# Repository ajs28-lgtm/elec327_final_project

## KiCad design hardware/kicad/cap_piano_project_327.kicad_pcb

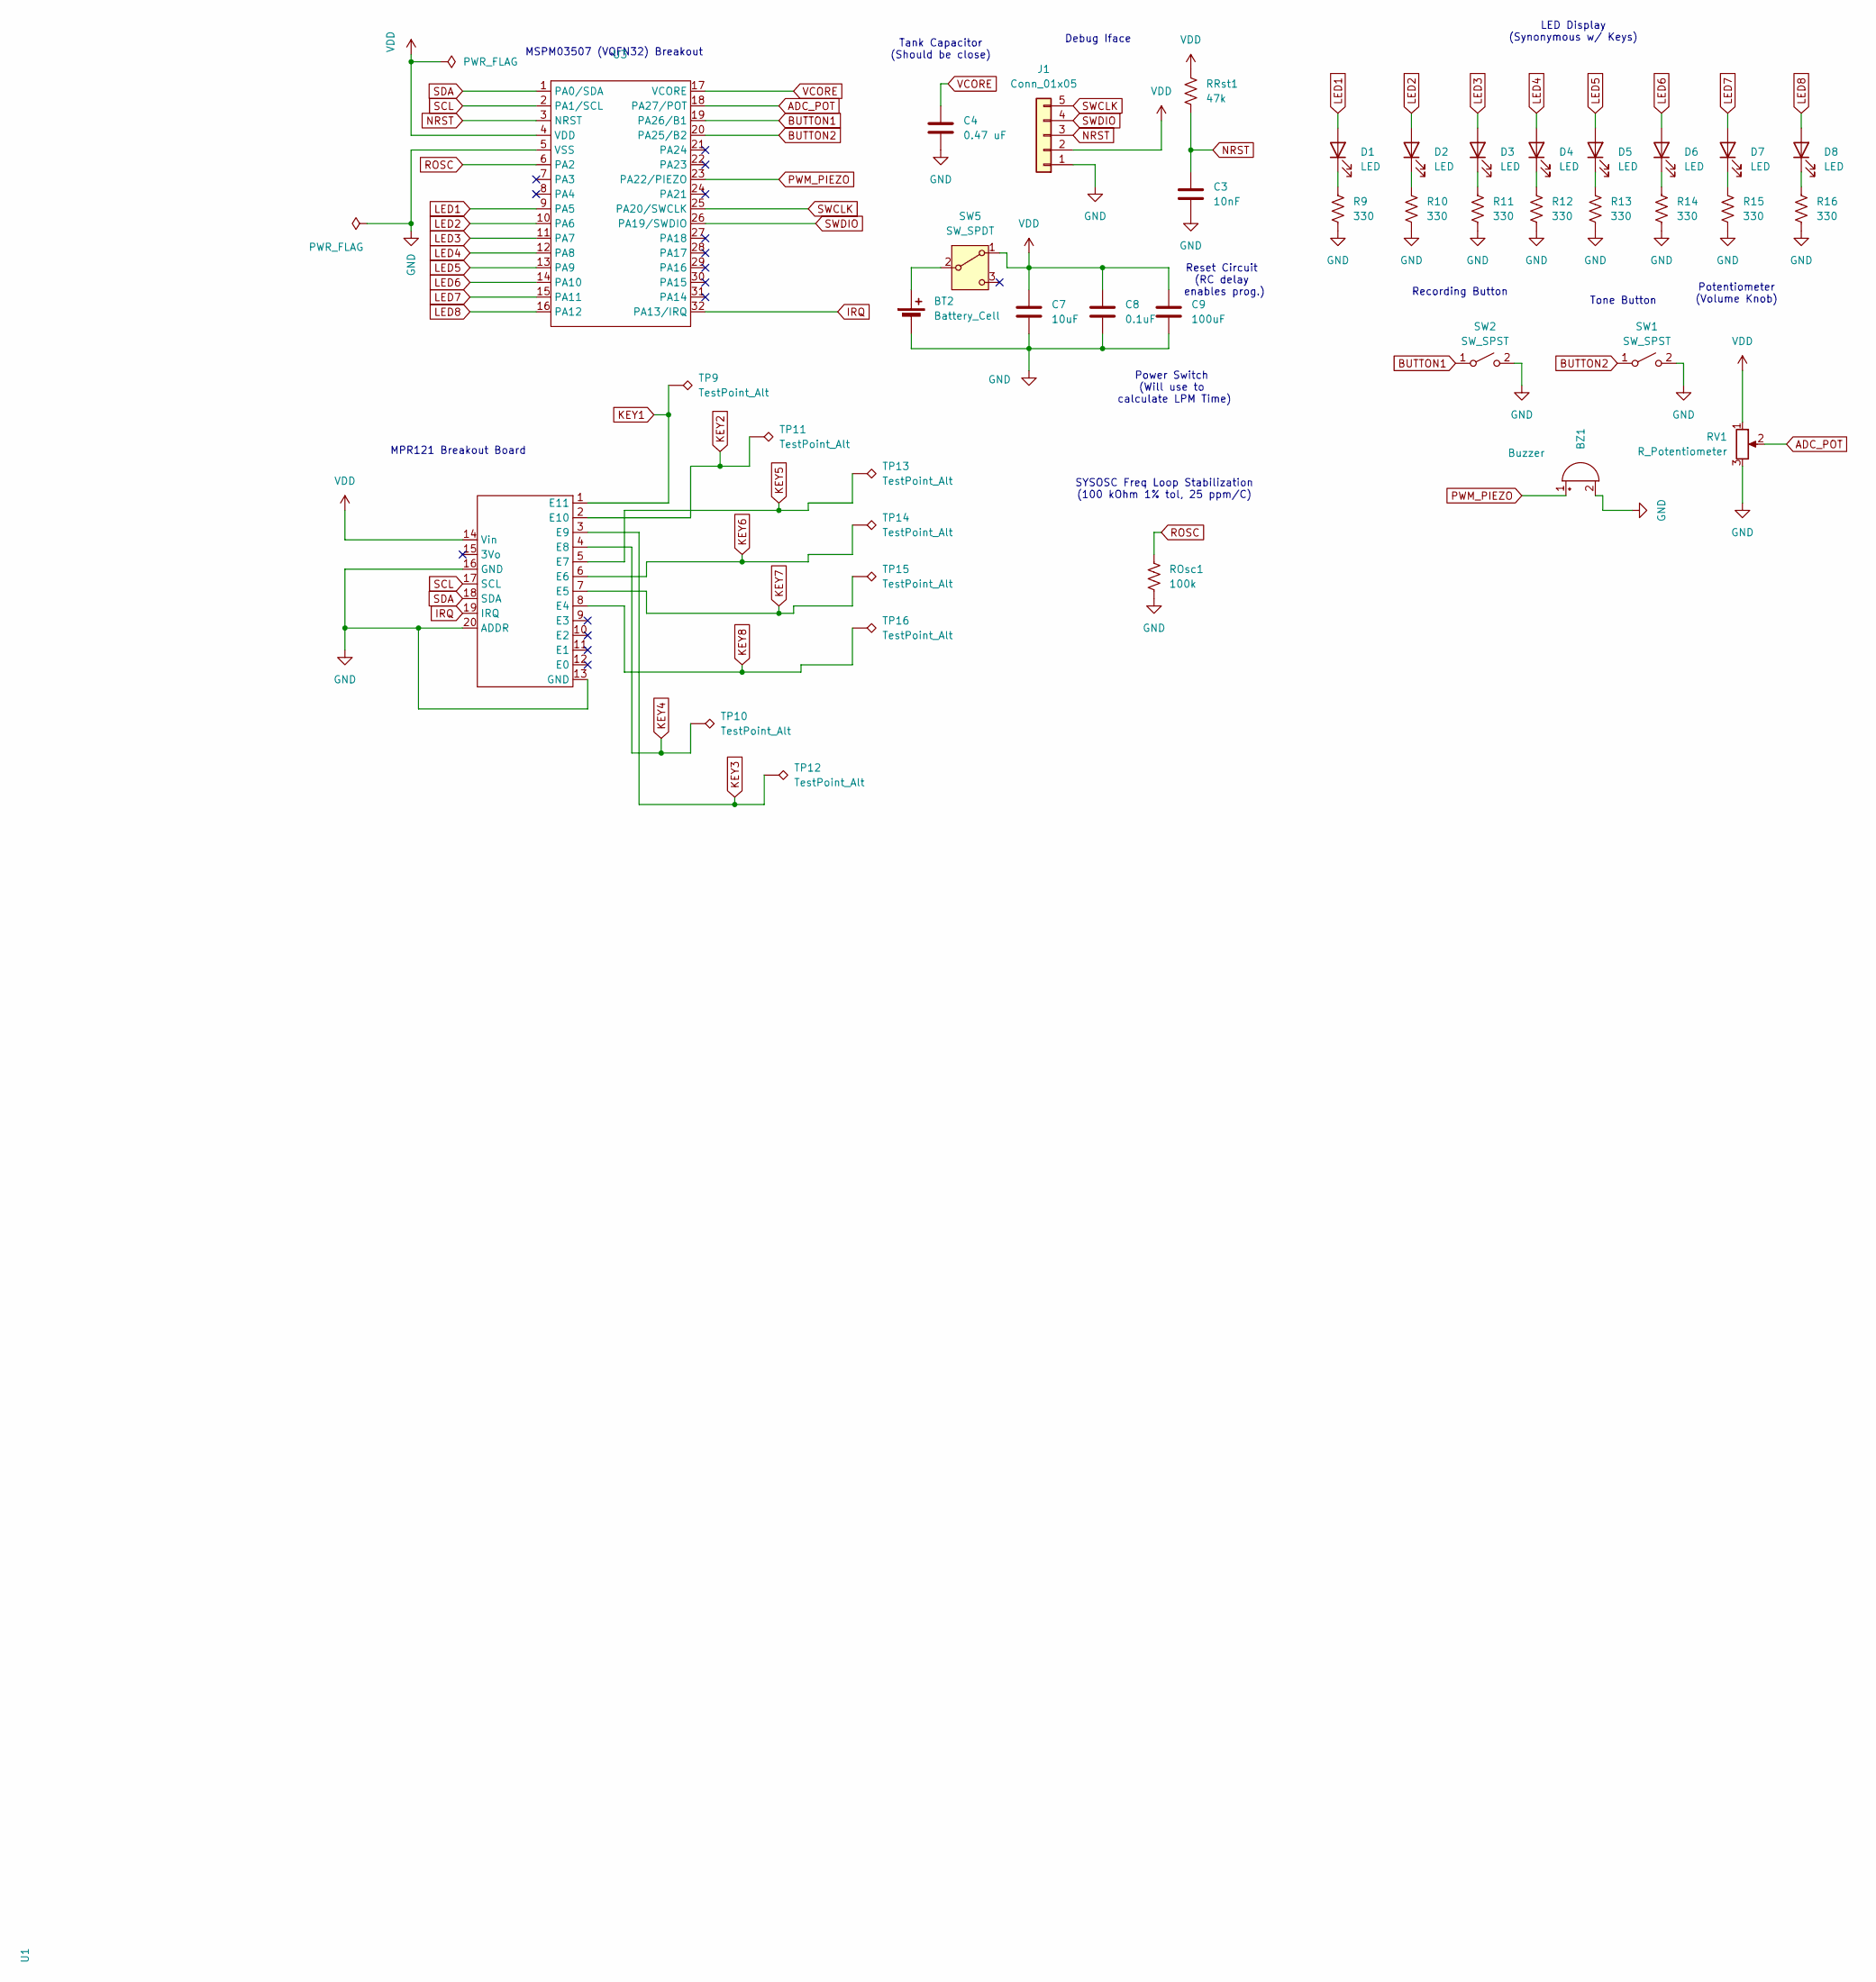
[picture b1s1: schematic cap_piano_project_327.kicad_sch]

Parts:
BT2: Battery_Cell; BatteryHolder_Keystone_1060_1x2032; MPN C7498148; LCSC Part # C7498148
BZ1: Buzzer; Buzzer_TDK_PS1240P02BT_D12.2mm_H6.5mm
C3: 10nF; C_1206_3216Metric_Pad1.33x1.80mm_HandSolder
C4: 0.47 uF; C_1206_3216Metric_Pad1.33x1.80mm_HandSolder
C7: 10uF; C_1206_3216Metric_Pad1.33x1.80mm_HandSolder; LCSC Part # C19702
C8: 0.1uF; C_1206_3216Metric_Pad1.33x1.80mm_HandSolder; LCSC Part # C1591
C9: 100uF; C_1206_3216Metric_Pad1.33x1.80mm_HandSolder; LCSC Part # C15008
D1, D2, D3, D4, D5, D6, D7, D8: LED; LED_D5.0mm
J1: Conn_01x05; PinHeader_1x05_P2.54mm_Vertical; MPN C492413
R9, R10, R11, R12, R13, R14, R15, R16: 330; R_1206_3216Metric
ROsc1: 100k; R_1206_3216Metric
RRst1: 47k; R_1206_3216Metric
RV1: R_Potentiometer; Potentiometer_Alpha_RD901F-40-00D_Single_Vertical
SW1, SW2: SW_SPST; SW_PUSH_6mm_H5mm
SW5: SW_SPDT; SW_Slide-03_Wuerth-WS-SLTV_10x2.5x6.4_P2.54mm; MPN C20611678; LCSC Part # C20611678
TP9, TP10, TP11, TP12, TP13, TP14, TP15, TP16: TestPoint_Alt; TestPoint_Pad_4.0x4.0mm
U1: Adafruit_MPR121_1982_Socket
U3: SMT Breakout PCB - 32-QFN

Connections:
ADC_POT: RV1.2, U3.18 (PA27/POT)
BUTTON1: SW2.1 (A), U3.19 (PA26/B1)
BUTTON2: SW1.1 (A), U3.20 (PA25/B2)
GND: BT2.2 (-), BZ1.2 (-), C3.2, C4.2, C7.2, C8.2, C9.2, J1.1, R9.1, R10.1, R11.1, R12.1, R13.1, R14.1, R15.1, R16.1, ROsc1.1, RV1.3, SW1.2 (B), SW2.2 (B), U1.13 (GND), U1.16 (GND), U1.20 (ADDR), U3.5 (VSS)
IRQ: U1.19 (IRQ), U3.32 (PA13/IRQ)
KEY1: TP9.1, U1.1 (E11)
KEY2: TP11.1, U1.2 (E10)
KEY3: TP12.1, U1.3 (E9)
KEY4: TP10.1, U1.4 (E8)
KEY5: TP13.1, U1.5 (E7)
KEY6: TP14.1, U1.6 (E6)
KEY7: TP15.1, U1.7 (E5)
KEY8: TP16.1, U1.8 (E4)
LED1: D1.2 (A), U3.9 (PA5)
LED2: D2.2 (A), U3.10 (PA6)
LED3: D3.2 (A), U3.11 (PA7)
LED4: D4.2 (A), U3.12 (PA8)
LED5: D5.2 (A), U3.13 (PA9)
LED6: D6.2 (A), U3.14 (PA10)
LED7: D7.2 (A), U3.15 (PA11)
LED8: D8.2 (A), U3.16 (PA12)
NRST: C3.1, J1.3, RRst1.1, U3.3 (NRST)
unnamed: BT2.1 (+), SW5.2 (B)
unnamed: D1.1 (K), R9.2
unnamed: D2.1 (K), R10.2
unnamed: D3.1 (K), R11.2
unnamed: D4.1 (K), R12.2
unnamed: D5.1 (K), R13.2
unnamed: D6.1 (K), R14.2
unnamed: D7.1 (K), R15.2
unnamed: D8.1 (K), R16.2
PWM_PIEZO: BZ1.1 (+), U3.23 (PA22/PIEZO)
ROSC: ROsc1.2, U3.6 (PA2)
SCL: U1.17 (SCL), U3.2 (PA1/SCL)
SDA: U1.18 (SDA), U3.1 (PA0/SDA)
SWCLK: J1.5, U3.25 (PA20/SWCLK)
SWDIO: J1.4, U3.26 (PA19/SWDIO)
VCORE: C4.1, U3.17 (VCORE)
VDD: C7.1, C8.1, C9.1, J1.2, RRst1.2, RV1.1, SW5.1 (A), U1.14 (Vin), U3.4 (VDD)

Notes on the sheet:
Power Switch (Will use to calculate LPM Time)
Recording Button
LED Display (Synonymous w/ Keys)
SYSOSC Freq Loop Stabilization (100 kOhm 1% tol, 25 ppm/C)
MSPM03507 (VQFN32) Breakout
Tank Capacitor (Should be close)
Potentiometer (Volume Knob)
Tone Button
Debug Iface
MPR121 Breakout Board
Reset Circuit (RC delay enables prog.)

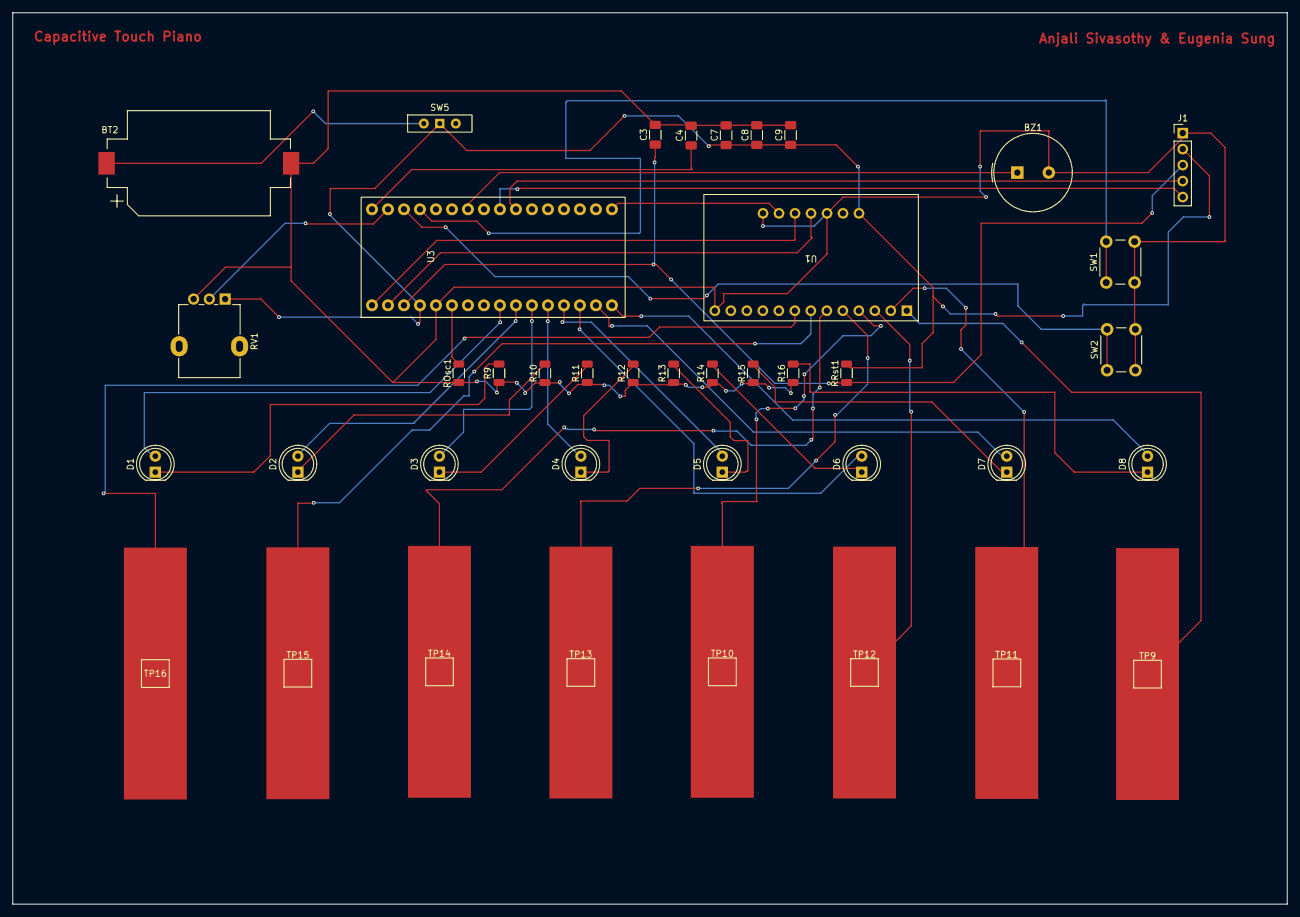
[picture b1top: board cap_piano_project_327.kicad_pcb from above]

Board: 2 copper layers, 202.4 x 141.5 mm, 40 parts (0 on the bottom side), 39 nets.

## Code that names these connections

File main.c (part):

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// HARDWARE DEFINITIONS & PIN MAPPING
// ============================================================================

// LEDs (PA5 to PA12)
#define LED1 (1u << 5)
#define LED2 (1u << 6)
#define LED3 (1u << 7)
#define LED4 (1u << 8)
#define LED5 (1u << 9)
#define LED6 (1u << 10)
#define LED7 (1u << 11)
#define LED8 (1u << 12)
#define LED_ALL (LED1 | LED2 | LED3 | LED4 | LED5 | LED6 | LED7 | LED8)

// Buzzer (PA22)
#define BUZZER (1u << 22)

// I2C and IRQ Pins
#define SDA_PIN (1u << 0)  // PA0
#define SCL_PIN (1u << 1)  // PA1
#define IRQ_PIN (1u << 13) // PA13

// Buttons are wired to GND
// They are active-low and need internal pull-ups
#define BUTTON_OCTAVE (1u << 26) // PA26 / BUTTON1
#define BUTTON_RECORD (1u << 25) // PA25 / BUTTON2
#define CONTROL_PINS (BUTTON_OCTAVE | BUTTON_RECORD)

// ADC potentiometer input
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
    // Configure PINCM for LEDs (Output)
    // 0x81 = PC (bit 7) + GPIO function (bit 0)
    IOMUX->SECCFG.PINCM[IOMUX_PINCM10] = 0x81; // PA5 LED1
    IOMUX->SECCFG.PINCM[IOMUX_PINCM11] = 0x81; // PA6 LED2
    IOMUX->SECCFG.PINCM[IOMUX_PINCM14] = 0x81; // PA7 LED3
    IOMUX->SECCFG.PINCM[IOMUX_PINCM19] = 0x81; // PA8 LED4
    IOMUX->SECCFG.PINCM[IOMUX_PINCM20] = 0x81; // PA9 LED5
    IOMUX->SECCFG.PINCM[IOMUX_PINCM21] = 0x81; // PA10 LED6
    IOMUX->SECCFG.PINCM[IOMUX_PINCM22] = 0x81; // PA11 LED7
    IOMUX->SECCFG.PINCM[IOMUX_PINCM34] = 0x81; // PA12 LED8

    // Configure PINCM for Buzzer (Output)
    IOMUX->SECCFG.PINCM[IOMUX_PINCM47] = 0x81; // PA22

    // Configure PINCM for MPR121 IRQ (Input)
    // CRITICAL FIX: Must set INENA (bit 18) to enable the input buffer!
    // 0x40081 = INENA (bit 18) + PC (bit 7) + GPIO function (bit 0)
    IOMUX->SECCFG.PINCM[IOMUX_PINCM35] = 0x40081; // PA13

    // Configure PINCM for Soft I2C (Open-Drain style)
    // Also need INENA (bit 18) so we can read SDA/SCL state
    IOMUX->SECCFG.PINCM[IOMUX_PINCM1] = 0x40081; // PA0 SDA
    IOMUX->SECCFG.PINCM[IOMUX_PINCM2] = 0x40081; // PA1 SCL

    // Configure user buttons as GPIO inputs with pull-ups
    // 0x60081 = pull-up + input enable + peripheral connected + GPIO function
    // PA26 is PINCM59 and PA25 is PINCM55 on MSPM0G3507
    IOMUX->SECCFG.PINCM[IOMUX_PINCM59] = 0x60081; // PA26 / BUTTON1 / octave
    IOMUX->SECCFG.PINCM[IOMUX_PINCM55] = 0x60081; // PA25 / BUTTON2 / record

    // Configure PA27/POT for analog use
    // For analog functions, PINCM.PF and PINCM.PC should be 0, 
    // so do not connect it as a digital GPIO
    IOMUX->SECCFG.PINCM[IOMUX_PINCM60] = 0x00000000; // PA27 / A0_0

    // Set output values to 0 initially
    GPIOA->DOUTCLR31_0 = LED_ALL | BUZZER | SDA_PIN | SCL_PIN;
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    DL_ADC12_setSampleTime0(ADC0, 32);
    DL_ADC12_configConversionMem(ADC0,
                                 DL_ADC12_MEM_IDX_0,
                                 DL_ADC12_INPUT_CHAN_0, // PA27 / A0_0
                                 DL_ADC12_REFERENCE_VOLTAGE_VDDA,
                                 DL_ADC12_SAMPLE_TIMER_SOURCE_SCOMP0,
                                 DL_ADC12_AVERAGING_MODE_DISABLED,
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        // Diagnostic: Init Failed
        // Blink LED1 and LED8 alternately
        while (1) {
            GPIOA->DOUTSET31_0 = LED1;
            GPIOA->DOUTCLR31_0 = LED8;
            delay_ms(250);
            GPIOA->DOUTCLR31_0 = LED1;
            GPIOA->DOUTSET31_0 = LED8;
            delay_ms(250);
        }
    }
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            // Diagnostic: I2C Read Failed during loop
            // Blink LED1 and LED2 rapidly to indicate read error
            GPIOA->DOUTCLR31_0 = LED_ALL;
            GPIOA->DOUTSET31_0 = LED1 | LED2;
            delay_ms(100);
            GPIOA->DOUTCLR31_0 = LED1 | LED2;
            delay_ms(100);
        }
    }
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
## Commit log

2026-05-03 Add project website
2026-05-03 Trigger workflow on website branch
2026-05-04 Initial KiCad project
2026-05-04 Organize firmware and KiCad files
2026-05-04 Add demo videos
2026-05-04 Fix video embedding
2026-05-04 Added comments to I2C
2026-05-05 Update main.c
    Added comments to buttons and pot
2026-05-05 Update cloc_summary.txt
    Updated cloc summary
2026-05-05 Update cloc_summary.txt
    Updated cloc_summary
2026-05-05 Update project website
2026-05-05 Move site to docs for GitHub Pages
